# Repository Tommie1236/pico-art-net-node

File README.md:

# !! working on v2. the main branch is deprecated if you see this message. please go to [the V2 branch](https://github.com/Tommie1236/pico-art-net-node/tree/V2).

# pico-art-net-node

got the idea from the project linked below. took some ideas/parts off it and created my own one 

https://www.techandtransit.com/lighting/pi-pico-artnet-to-dmx-node  
https://github.com/tmingos/Pico-ArtNet-DMX-Node

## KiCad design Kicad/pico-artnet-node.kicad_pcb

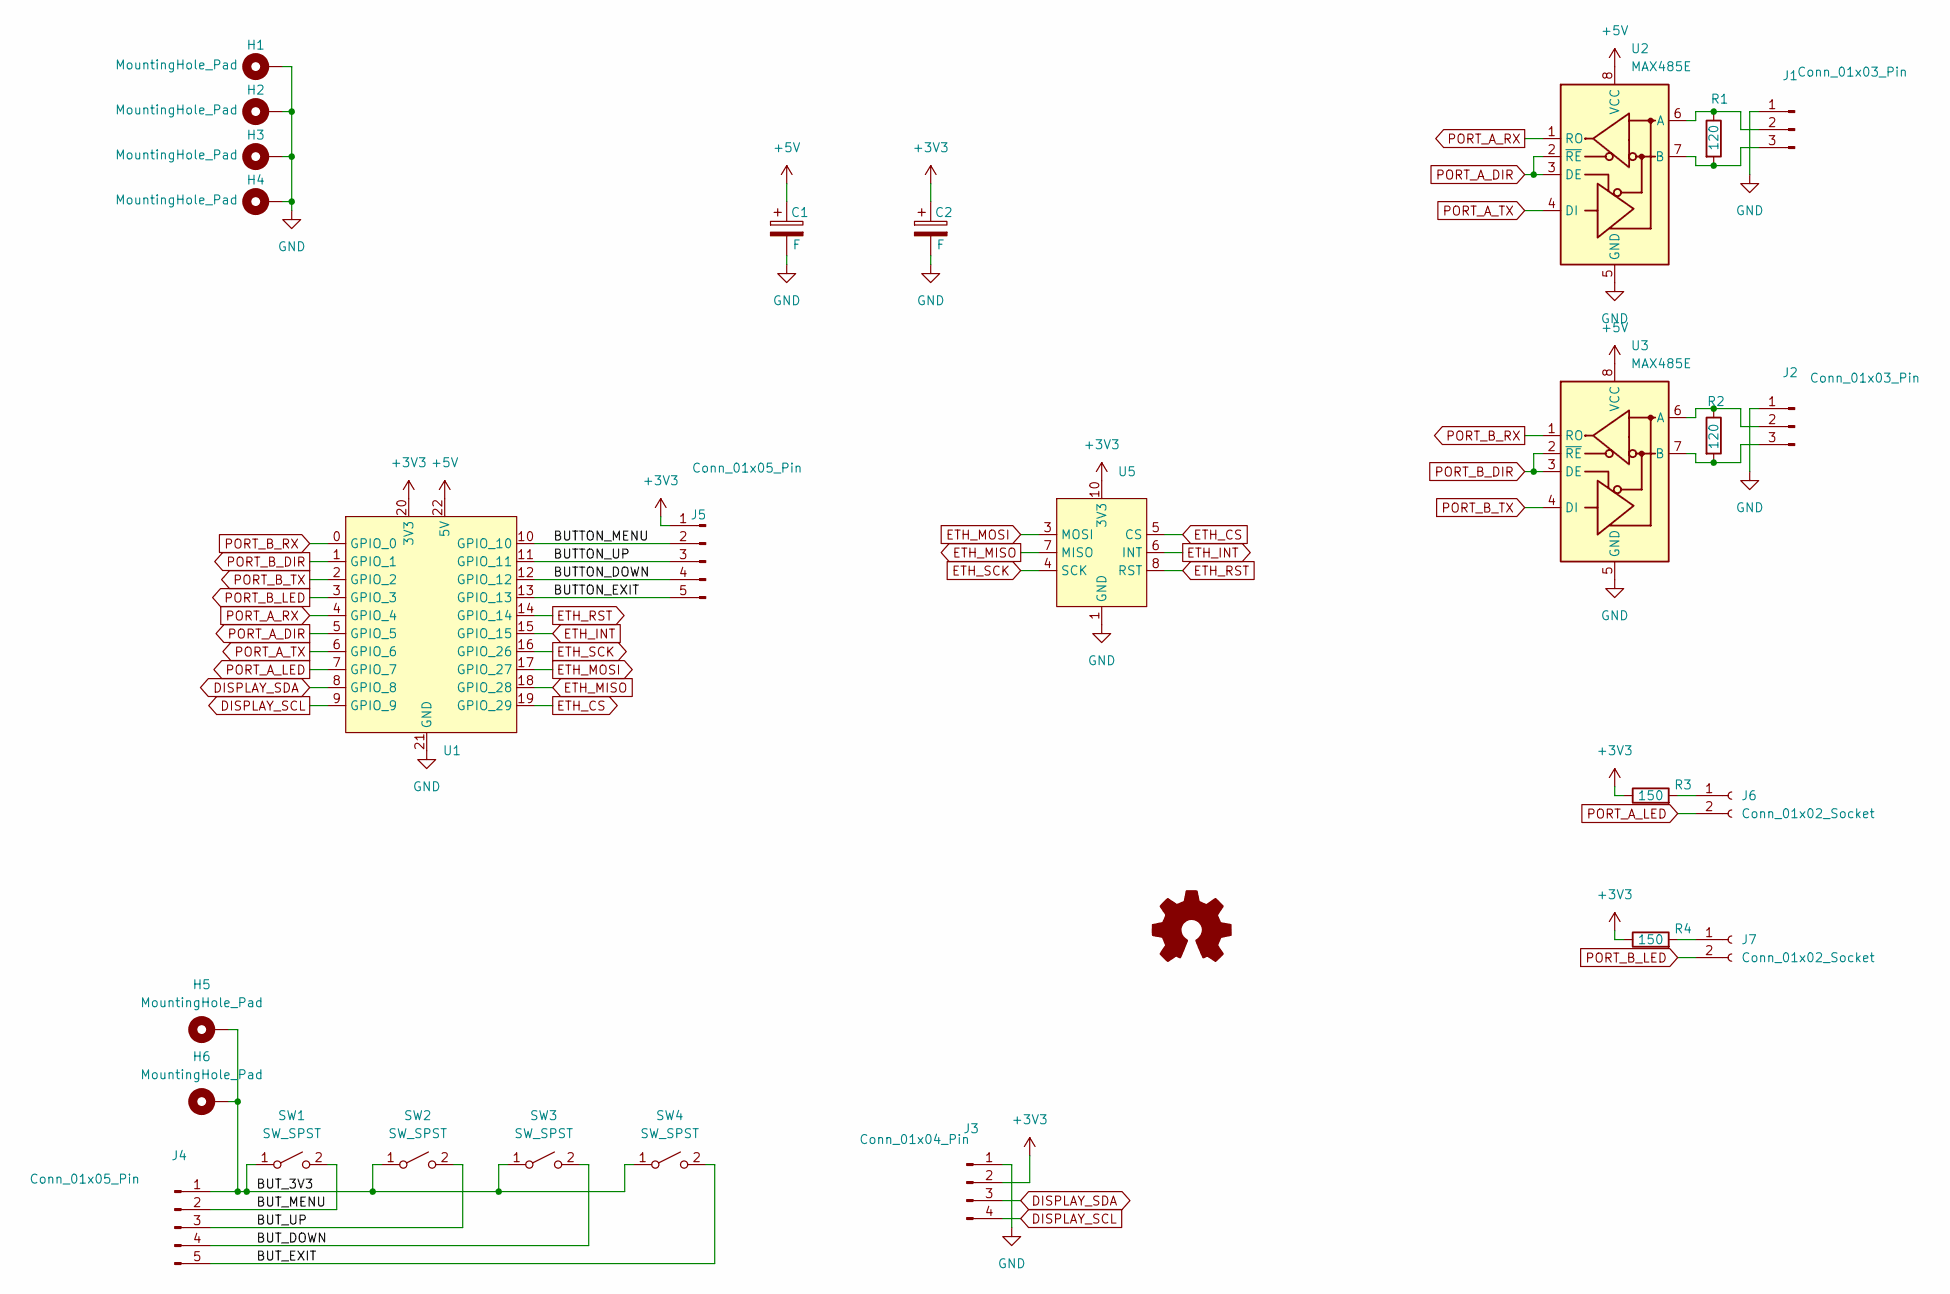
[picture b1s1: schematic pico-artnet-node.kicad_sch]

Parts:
C1, C2: F; CP_Radial_D5.0mm_P2.50mm
H1, H2, H3, H4, H5, H6: MountingHole_Pad; MountingHole_3.2mm_M3_DIN965_Pad
J1, J2: Conn_01x03_Pin; PinHeader_1x03_P2.54mm_Vertical
J3: Conn_01x04_Pin; PinHeader_1x04_P2.54mm_Vertical
J4, J5: Conn_01x05_Pin; PinHeader_1x05_P2.54mm_Vertical
J6, J7: Conn_01x02_Socket; PinHeader_2x01_P2.54mm_Vertical
R1, R2: 120; R_Axial_DIN0207_L6.3mm_D2.5mm_P2.54mm_Vertical
R3, R4: 150; R_Axial_DIN0207_L6.3mm_D2.5mm_P2.54mm_Vertical
SW1, SW2, SW3, SW4: SW_SPST; SW_PUSH_6mm
SYM2: Logo_Open_Hardware_Small; OSHW-Logo2_14.6x12mm_SilkScreen
U1: RP2040-Zero
U2, U3: MAX485E; DIP-8_W7.62mm
U5: w5500

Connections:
+3V3: C2.1, J3.2, J5.1, R3.1, R4.1, U1.20 (3V3), U5.10 (3V3), U5.11 (3V3)
+5V: C1.1, U1.22 (5V), U2.8 (VCC), U3.8 (VCC)
/BUTTON_DOWN: J5.4, U1.12 (GPIO_12)
/BUTTON_EXIT: J5.5, U1.13 (GPIO_13)
/BUTTON_MENU: J5.2, U1.10 (GPIO_10)
/BUTTON_UP: J5.3, U1.11 (GPIO_11)
/BUT_3V3: H5.1, H6.1, J4.1, SW1.1 (A), SW2.1 (A), SW3.1 (A), SW4.1 (A)
/BUT_DOWN: J4.4, SW3.2 (B)
/BUT_EXIT: J4.5, SW4.2 (B)
/BUT_MENU: J4.2, SW1.2 (B)
/BUT_UP: J4.3, SW2.2 (B)
DISPLAY_SCL: J3.4, U1.9 (GPIO_9)
DISPLAY_SDA: J3.3, U1.8 (GPIO_8)
ETH_CS: U1.19 (GPIO_29), U5.5 (CS)
ETH_INT: U1.15 (GPIO_15), U5.6 (INT)
ETH_MISO: U1.18 (GPIO_28), U5.7 (MISO)
ETH_MOSI: U1.17 (GPIO_27), U5.3 (MOSI)
ETH_RST: U1.14 (GPIO_14), U5.8 (RST)
ETH_SCK: U1.16 (GPIO_26), U5.4 (SCK)
GND: C1.2, C2.2, H1.1, H2.1, H3.1, H4.1, J1.1, J2.1, J3.1, U1.21 (GND), U2.5 (GND), U3.5 (GND), U5.1 (GND), U5.2 (GND), U5.12 (GND)
unnamed: J1.2, R1.1, U2.6 (A)
unnamed: J1.3, R1.2, U2.7 (B)
unnamed: J2.2, R2.1, U3.6 (A)
unnamed: J2.3, R2.2, U3.7 (B)
unnamed: J6.1, R3.2
unnamed: J7.1, R4.2
PORT_A_DIR: U1.5 (GPIO_5), U2.2 (~RE), U2.3 (DE)
PORT_A_LED: J6.2, U1.7 (GPIO_7)
PORT_A_RX: U1.4 (GPIO_4), U2.1 (RO)
PORT_A_TX: U1.6 (GPIO_6), U2.4 (DI)
PORT_B_DIR: U1.1 (GPIO_1), U3.2 (~RE), U3.3 (DE)
PORT_B_LED: J7.2, U1.3 (GPIO_3)
PORT_B_RX: U1.0 (GPIO_0), U3.1 (RO)
PORT_B_TX: U1.2 (GPIO_2), U3.4 (DI)

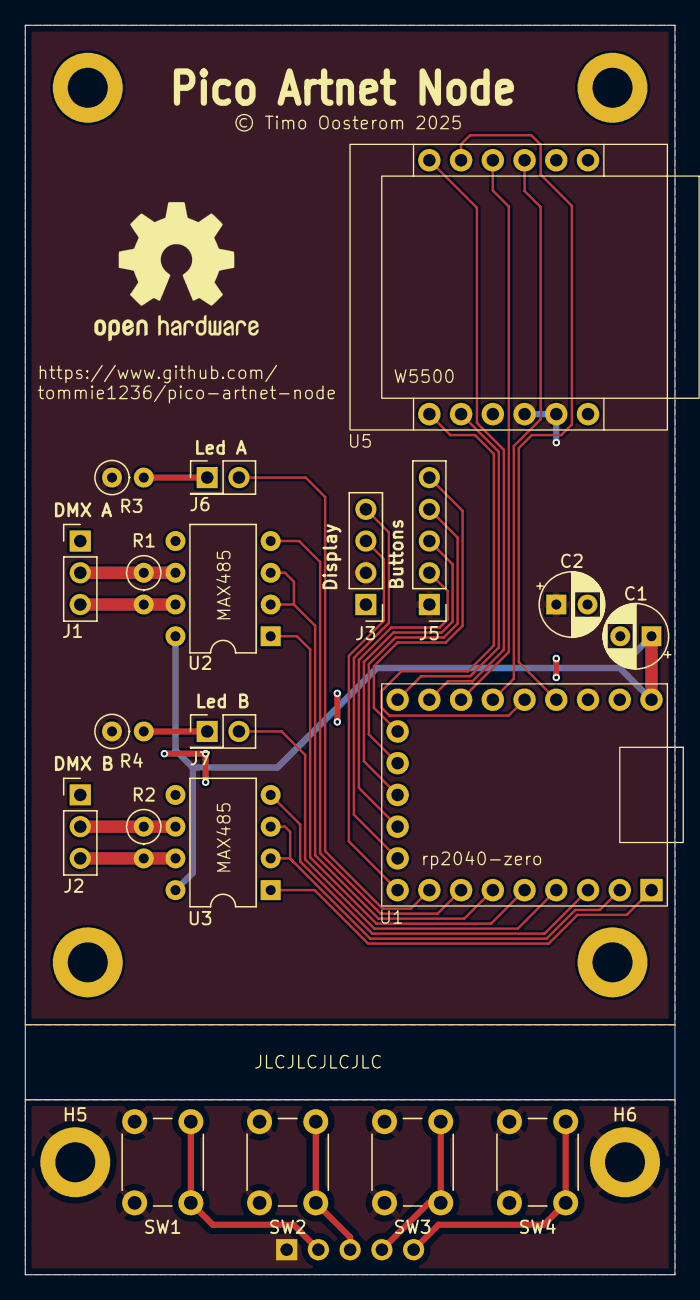
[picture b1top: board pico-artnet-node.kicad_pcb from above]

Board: 2 copper layers, 52.0 x 100.0 mm, 28 parts (1 on the bottom side), 34 nets.

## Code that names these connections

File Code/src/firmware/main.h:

// Config file for Pico Art-Net DMX Node
// ©Timo Oosterom 2024

// Config made for a RP2040 Zero. (Pi pico in smaller form factor)
// For full pin functions see: https://datasheets.raspberrypi.com/rp2040/rp2040-datasheet.pdf (Section 1.4.3)
//      
//                   ┏━━━━━┓              
//               ┏━━━┫     ┣━━━┓          
//            5V ┃◎  ┗━━━━━┛  ◎┃ GP0 PORT_B_RX    
//           Gnd ┃■           ◎┃ GP1 PORT_B_DIR    
//           3V3 ┃◎           ◎┃ GP2 PORT_B_TX 
// ETH_CS   GP29 ┃◎           ◎┃ GP3 PORT_B_LED        
// ETH_MOSI GP28 ┃◎           ◎┃ GP4 PORT_A_RX    
// ETH_MISO GP27 ┃◎     □     ◎┃ GP5 PORT_A_DIR    
// ETH_SCK  GP26 ┃◎     ┗GP16 ◎┃ GP6 PORT_A_TX 
// ETH_INT  GP15 ┃◎           ◎┃ GP7 PORT_A_LED
// ETH_RST  GP14 ┃◎ ◎ ◎ ◎ ◎ ◎ ◎┃ GP8 DISPLAY_SDA    
//               ┗━━━━━━━━━━━━━┛
//                  ┃ ┃ ┃ ┃ ┗ GP9    DISPLAY_SCL    
//                  ┃ ┃ ┃ ┗ GP10     MENU_BUTTON    
//                  ┃ ┃ ┗ GP11       UP_BUTTON
//                  ┃ ┗ GP12         DOWN_BUTTON
//                  ┗ GP13           EXIT_BUTTON
//
//  GP17-25 Are available via small pads on the bottom side of the board.

#ifndef MAIN_H
#define MAIN_H

// uncomment if you want debug output via usb serial, its automaticly disabled when using usb dmx
#define DEBUG_LOGGING

// Uncomment to enable serial usb dmx. !!Disables debug logging
// #define USB_SERIAL_DMX

// TODO: change back to official ip after development
#define CONFIG_DEFAULT_IP           (uint8_t[]) {192, 168, 2, 230}
// #define CONFIG_DEFAULT_IP           (uint8_t[]) {10, 0, 0, 1}
#define CONFIG_DEFAULT_SUBNET       (uint8_t[]) {255, 255, 255, 0}
#define CONFIG_DEFAULT_GATEWAY      (uint8_t[]) {0, 0, 0, 0}

// General
#define UNIVERSE_LENGTH 512

// DMX Ports
#define PORT_A_ENABLE   1
#define PORT_A_TX_PIN   6
#define PORT_A_RX_PIN   4
#define PORT_A_DIR_PIN  5
#define PORT_A_LED_PIN  7

#define PORT_B_ENABLE   1
#define PORT_B_TX_PIN   2
#define PORT_B_RX_PIN   0
#define PORT_B_DIR_PIN  1
#define PORT_B_LED_PIN  3

// Display
#define DISPLAY_WIDTH   128
#define DISPLAY_HEIGHT  32 // 64 or 32. don't know what i will go with yet

#define DISPLAY_SDA_PIN  8
#define DISPLAY_SCL_PIN  9

// Buttons/Controls. 
#define MENU_BUTTON_PIN 10  // Menu/Enter
#define UP_BUTTON_PIN   11  // Up
#define DOWN_BUTTON_PIN 12  // Down
#define EXIT_BUTTON_PIN 13  // Exit/Back

// Ethernet (w5500)
#define ETH_CS_PIN      29
#define ETH_MOSI_PIN    28
#define ETH_MISO_PIN    27
#define ETH_SCK_PIN     26
#define ETH_IRQ_PIN     15
#define ETH_RST_PIN     14
#define ETH_SPI         spi1


#ifdef USB_SERIAL_DMX
    #undef DEBUG_LOGGING
#endif // usb_serial_dmx

#endif // MAIN_H

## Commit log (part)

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2024-09-04 add vscode to .gitignore
2024-09-04 first working dmx output test
2024-09-04 add github test compile action
2024-09-04 forgot extra lib in gh action
2024-09-04 next action test
2024-09-04 add action status badge to readme
2024-09-08 add ssd1306 lib for ssd1315 i2c display
2024-09-08 fix(readme) : typo
    forgot double space for newline.
    keep forgetting that shit every time
2024-09-08 chore(readme) : shorten unnessesary long url
2024-09-10 move pygame project to pc with display and add py to gitignore
2024-09-10 added a ai start/template/example
2024-09-11 added some ui components
2024-09-11 changed to bitmap and added dmx-disabled
2024-11-24 sync earilier changes from sim. don't know what changed.
2024-11-24 Added config file and RP2040 pinout diagram
2024-11-24 add port en/disable option to config
2024-11-24 add some more info to pinout diagram
2024-11-24 fix some unicode characters displaying 2 wide on some systems and breaking the drawing
2024-11-25 removed unused code for rp2040-zero
2024-11-25 fix typo in main.h
2024-11-25 change "loading firmware ... to pico" to "RP2040" to make it more general
2024-11-25 moved the test from main to a test file
2024-11-25 started with setup and experimented with a display
2024-11-26 create i2c bus scanner because oled didn't have it's address written on it
2024-11-26 some more display testing. finally got them workinggit status
2024-11-27 added menu structure and implemented basic inefficent menu structure
2024-11-27 added forgotten enum classes before menu values
2024-11-27 moved current_selection reset to right places
2024-11-27 first working menu on the display
2024-11-27 updated build script to automaticly put rp2040 into bootsel mode and reboot after flash
    Yeey, no need to be pressing buttons and pluging/unplugging the usb anymore
2024-11-27 menu frontend almost completely finished.
    in process of cleaning the code up and making it more uniform/finish the menu front
2024-11-28 more progress on menu
2024-11-28 more menu progress
2024-11-30 finish port status menu's and config
2024-11-30 removed barely started similation for display
    started it because i couldn't get a display working and wanted to work on the menu. but fixed the hw and this wasn't really anywhere yet so i just deleted it
2024-12-01 chore: updated menu structure in comment to what is implemented in menu.
2024-12-01 changed ip config from string to uint8_t[4] and changed all checkmarks to x's
2024-12-01 fix: typo
2024-12-01 fix: typo agian
2024-12-01 really changed ip's from string to uint8_t arrays now. also little multicore test with static dmx output: :
2024-12-01 feat: implement ip changing from menu
2024-12-02 added universe selection for port A.
    compiles correctly but not yet tested on hw
2024-12-02 fix: subnet editing not worky worky
2024-12-08 added universe selction via display to both A and B
2024-12-08 fix: only load 15lowest bits to config and remove compile error
2024-12-08 finished menu for now. can and must be much improved but this works okay enough
2024-12-22 updated build script
2024-12-23 removed interfering python ignores as there isn't any python in this project anymore
2024-12-23 moved some things around after adding/removing libraries
2024-12-23 added artnet and ethernet libraries
2024-12-24 simplified build script
    removed a cd and submodule init for each module and just used one recursive init
2024-12-24 updated libraries
2024-12-24 updated libs and cmake for libs
    also changed board in build.sh as i am no longer using a pico-w
2025-07-03 fixed indentetion in main.cpp
2025-07-04 updated some comments
2025-07-05 cleaned up gitmodules
2025-07-06 artnet is finally working!! also cleaned up some code
2025-07-06 mac add. is now set by using the unique flash id
2025-07-06 changed picotool load to be more efficient by not overwriting matching portions of flash
2025-07-06 added labels to main.h pinout
2025-07-07 started pcb and switched port A/B pins for better layout
2025-07-08 swapped tx and led pins for better pcb layout
2025-07-12 finished pcb
2025-08-04 swapped miso and mosi lines so they connect correctly
2025-08-04 small comment edits. End of V1
2025-08-04 fix typo and very last version of V1
2025-08-04 moved old code away for reference
2025-08-04 Impl config structure and load/save from flash
2025-08-04 fixed compile test. default file
2025-08-11 small no documentive edits
2025-08-11 started porting the ssd1306 library to pure c
2025-08-12 changed some config structure/default values
2025-08-14 ssd1306 lib now has the base functions and basic shape rendering
2025-08-14 removed old cpp libraries
2025-08-20 small updated to oled library
2025-08-22 fixed build script and included other files
2025-08-22 fixed and updated config.c/h
2025-08-27 added .gitignore
2025-08-27 started artnet and dmx porting
2025-08-27 added compile commands for clangd
2025-08-27 updated to 2 universes and fixed some pin definitions
2025-09-07 progress in artnet porting and small change in config
2025-09-07 forgot to add config.h
2025-09-20 updated pcb
2025-09-22 mostly implemented artnet only need to integrate it with dmx when that finishes
2025-09-22 progress in menu state machine
2025-09-22 some general small updates
2025-12-05 got artnet rx working. artpoll reply not yet
2025-12-23 updated depencencies
2025-12-23 first dmx output from artnet working
2025-12-23 removed dependencies that broke github actions
2026-05-02 fixed submodules
2026-05-02 fixed artPollRelay + added artIpPorg (untested). + updated config to use default ip settings from header
2026-05-02 fixed picotool in build script
2026-05-02 fixed github ci?
2026-05-02 fixed github ci?(2)
2026-05-02 artIpProg now updates w5500 settings, added some artPollReply fields.
2026-05-06 added debug log define and general cleanup
2026-05-06 Update README to indicate V2 branch and deprecation
2026-05-16 implemented dynamic port mode switching. (Input code not implemented yet but is supported)
2026-06-05 added menu design and updated menu icons
2026-06-05 added sACN "logo"

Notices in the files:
Kicad/pico-artnet-node.kicad_pcb:
© Timo Oosterom 2025
